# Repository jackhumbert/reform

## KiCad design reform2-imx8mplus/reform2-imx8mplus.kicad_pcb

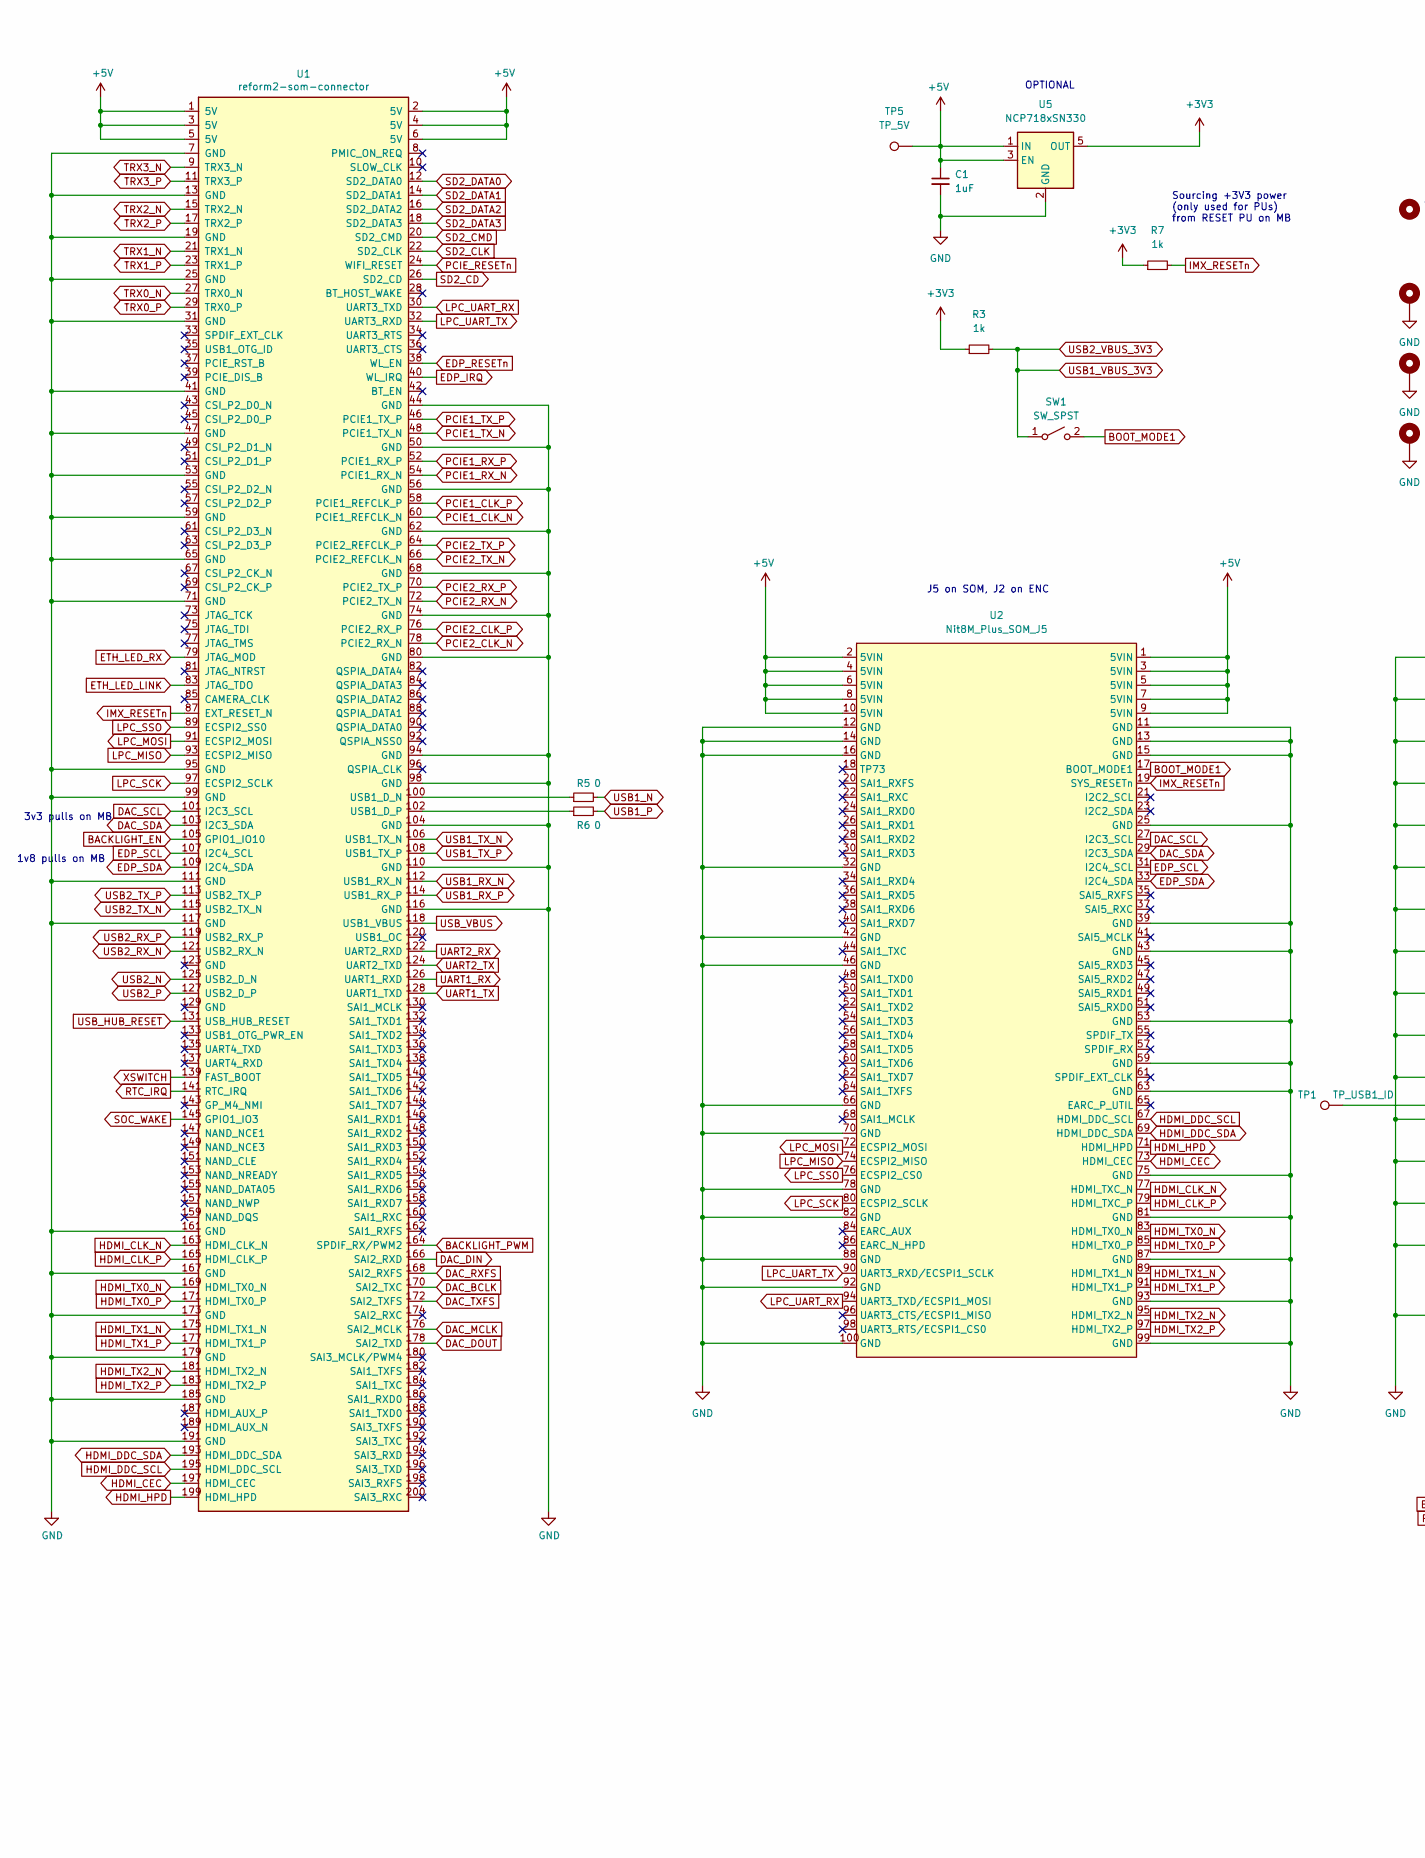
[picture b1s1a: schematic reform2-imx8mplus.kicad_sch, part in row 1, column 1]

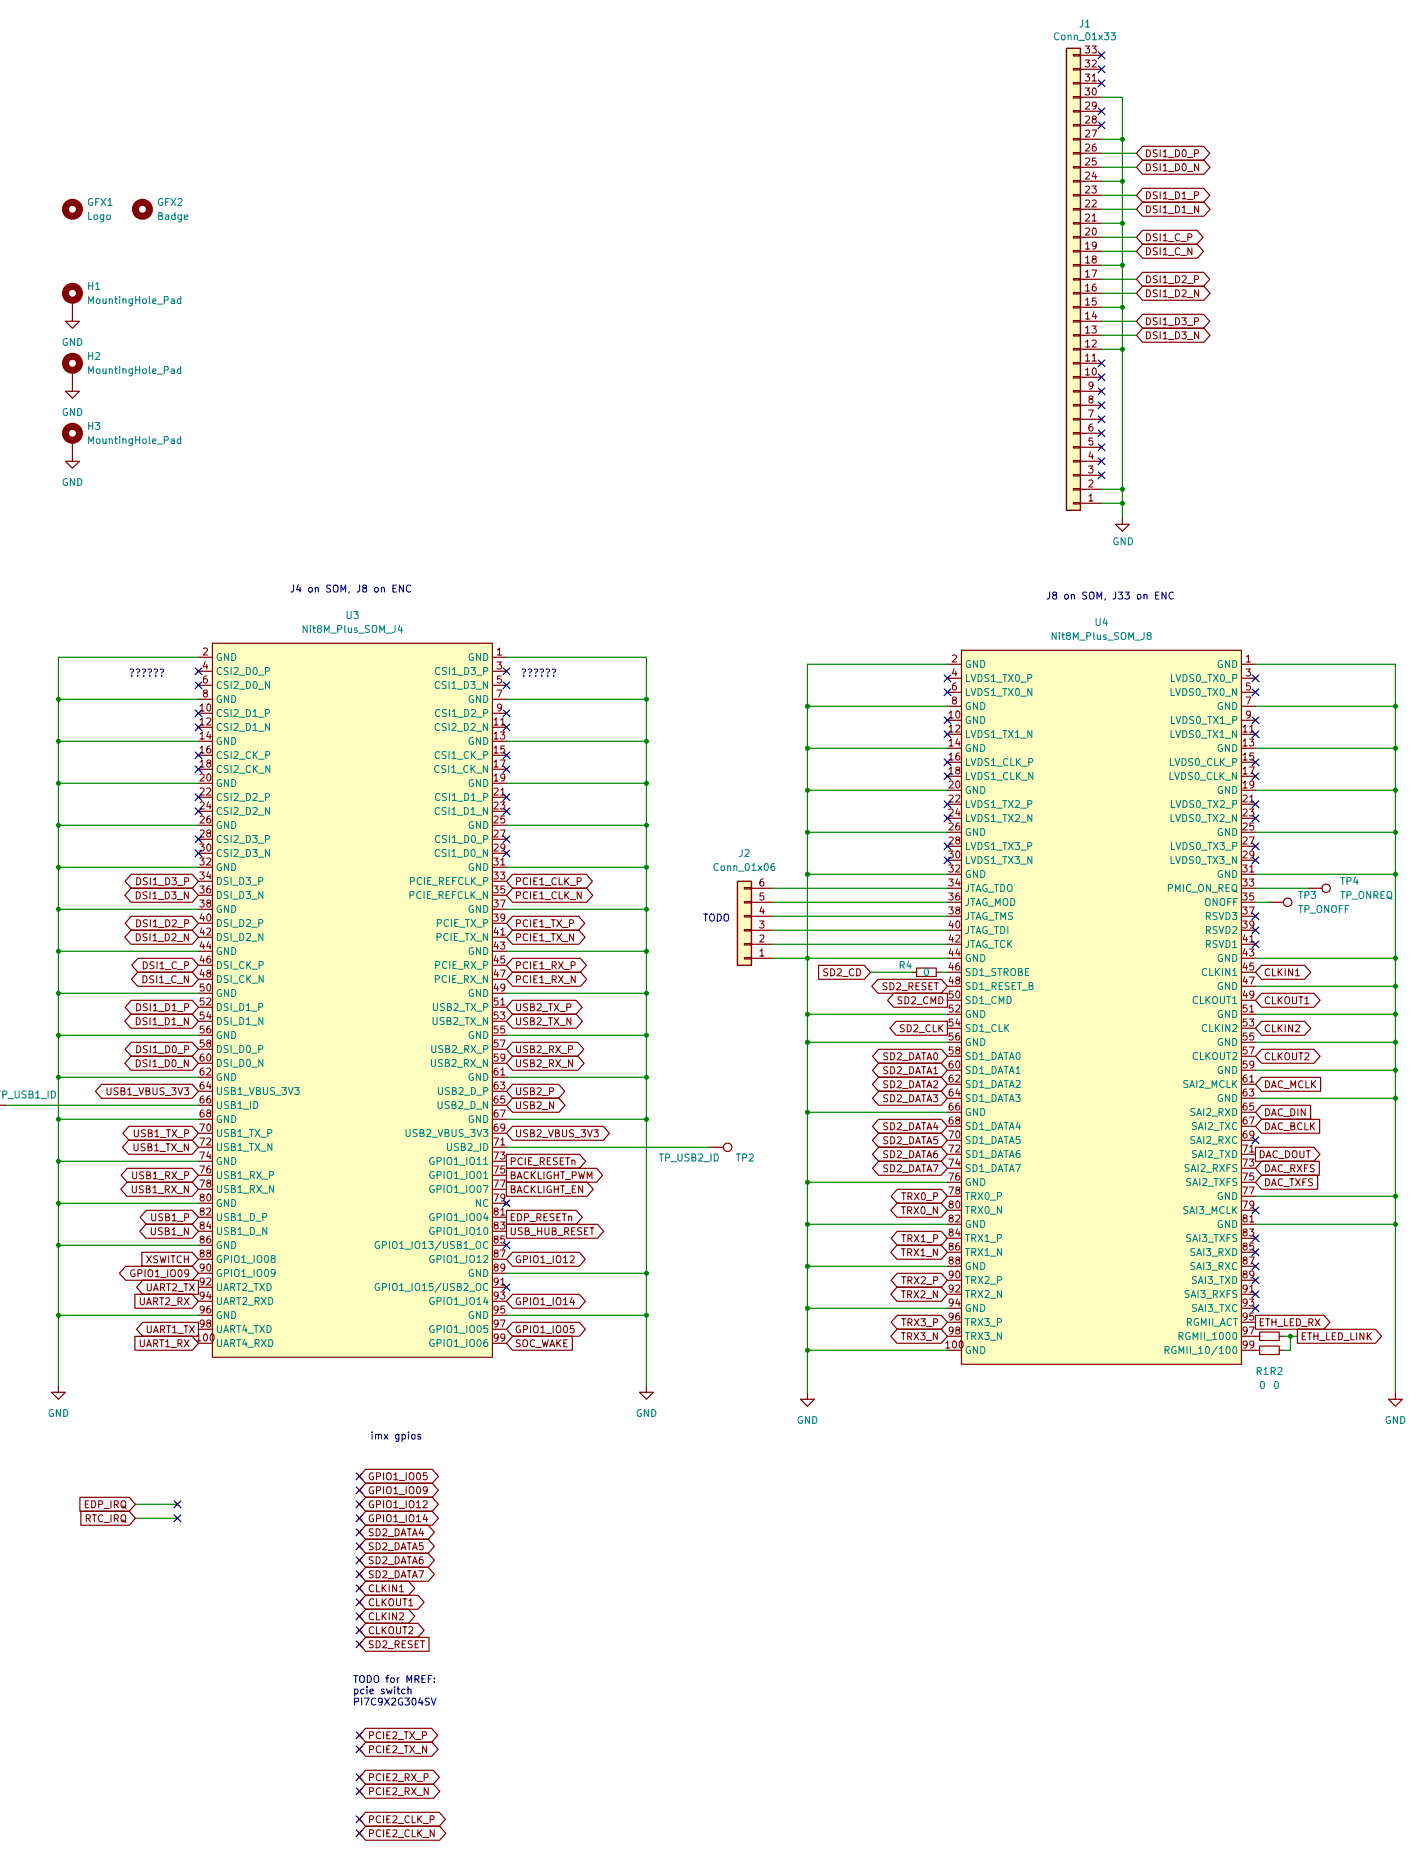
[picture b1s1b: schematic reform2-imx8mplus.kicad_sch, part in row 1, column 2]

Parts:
C1: 1uF; C_0603_1608Metric
GFX1: Logo; mntreform
GFX2: Badge; reform2-imx8mplus-badge
H1, H2, H3: MountingHole_Pad; MountingHole_2.2mm_M2_DIN965_Pad
J1: Conn_01x33; Hirose_FH12-33S-0.5SH_1x33-1MP_P0.50mm_Horizontal; MPN FH12-33S-0.5SH
J2: Conn_01x06; PinHeader_1x06_P2.00mm_Vertical
R1, R2, R5, R6: 0; R_0603_1608Metric
R3, R7: 1k; C_0603_1608Metric
R4: 0; C_0603_1608Metric
SW1: SW_SPST; PinHeader_1x02_P2.00mm_Horizontal
TP1: TP_USB1_ID; TestPoint_Pad_1.0x1.0mm
TP2: TP_USB2_ID; TestPoint_Pad_1.0x1.0mm
TP3: TP_ONOFF; TestPoint_Pad_1.0x1.0mm
TP4: TP_ONREQ; TestPoint_Pad_1.0x1.0mm
TP5: TP_5V; TestPoint_Pad_1.0x1.0mm
U1: reform2-som-connector; ddr2-sodimm200; MPN DNP
U2: Nit8M_Plus_SOM_J5; HRS_DF40C-100DS-0.4V(51)
U3: Nit8M_Plus_SOM_J4; HRS_DF40C-100DS-0.4V(51)
U4: Nit8M_Plus_SOM_J8; HRS_DF40C-100DS-0.4V(51)
U5: NCP718xSN330; SOT-23-5

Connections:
+3V3: R3.1, R7.1, U5.5 (OUT)
+5V: C1.1, TP5.1, U1.1 (5V), U1.2 (5V), U1.3 (5V), U1.4 (5V), U1.5 (5V), U1.6 (5V), U2.1 (5VIN), U2.2 (5VIN), U2.3 (5VIN), U2.4 (5VIN), U2.5 (5VIN), U2.6 (5VIN), U2.7 (5VIN), U2.8 (5VIN), U2.9 (5VIN), U2.10 (5VIN), U5.1 (IN), U5.3 (EN)
BACKLIGHT_EN: U1.105 (GPIO1_IO10), U3.77 (GPIO1_IO07)
BACKLIGHT_PWM: U1.164 (SPDIF_RX/PWM2), U3.75 (GPIO1_IO01)
BOOT_MODE1: SW1.2 (B), U2.17 (BOOT_MODE1)
CLKIN1: U4.45 (CLKIN1)
CLKIN2: U4.53 (CLKIN2)
CLKOUT1: U4.49 (CLKOUT1)
CLKOUT2: U4.57 (CLKOUT2)
DAC_BCLK: U1.170 (SAI2_TXC), U4.67 (SAI2_TXC)
DAC_DIN: U1.166 (SAI2_RXD), U4.65 (SAI2_RXD)
DAC_DOUT: U1.178 (SAI2_TXD), U4.71 (SAI2_TXD)
DAC_MCLK: U1.176 (SAI2_MCLK), U4.61 (SAI2_MCLK)
DAC_RXFS: U1.168 (SAI2_RXFS), U4.73 (SAI2_RXFS)
DAC_SCL: U1.101 (I2C3_SCL), U2.27 (I2C3_SCL)
DAC_SDA: U1.103 (I2C3_SDA), U2.29 (I2C3_SDA)
DAC_TXFS: U1.172 (SAI2_TXFS), U4.75 (SAI2_TXFS)
DSI1_C_N: J1.19, U3.48 (DSI_CK_N)
DSI1_C_P: J1.20, U3.46 (DSI_CK_P)
DSI1_D0_N: J1.25, U3.60 (DSI_D0_N)
DSI1_D0_P: J1.26, U3.58 (DSI_D0_P)
DSI1_D1_N: J1.22, U3.54 (DSI_D1_N)
DSI1_D1_P: J1.23, U3.52 (DSI_D1_P)
DSI1_D2_N: J1.16, U3.42 (DSI_D2_N)
DSI1_D2_P: J1.17, U3.40 (DSI_D2_P)
DSI1_D3_N: J1.13, U3.36 (DSI_D3_N)
DSI1_D3_P: J1.14, U3.34 (DSI_D3_P)
EDP_IRQ: U1.40 (WL_IRQ)
EDP_RESETn: U1.38 (WL_EN), U3.81 (GPIO1_IO04)
EDP_SCL: U1.107 (I2C4_SCL), U2.31 (I2C4_SCL)
EDP_SDA: U1.109 (I2C4_SDA), U2.33 (I2C4_SDA)
ETH_LED_LINK: R1.2, R2.2, U1.83 (JTAG_TDO)
ETH_LED_RX: U1.79 (JTAG_MOD), U4.95 (RGMII_ACT)
GND: C1.2, H1.1, H2.1, H3.1, J1.1, J1.2, J1.12, J1.15, J1.18, J1.21, J1.24, J1.27, J1.30, J2.1, U1.7 (GND), U1.13 (GND), U1.19 (GND), U1.25 (GND), U1.31 (GND), U1.41 (GND), U1.44 (GND), U1.47 (GND), U1.50 (GND), U1.53 (GND), U1.56 (GND), U1.59 (GND), U1.62 (GND), U1.65 (GND), U1.68 (GND), U1.71 (GND), U1.74 (GND), U1.80 (GND), U1.94 (GND), U1.95 (GND), U1.98 (GND), U1.99 (GND), U1.104 (GND), U1.110 (GND), U1.111 (GND), U1.116 (GND), U1.117 (GND), U1.161 (GND), U1.167 (GND), U1.173 (GND), U1.179 (GND), U1.185 (GND), U1.191 (GND), U2.11 (GND), U2.12 (GND), U2.13 (GND), U2.14 (GND), U2.15 (GND), U2.16 (GND), U2.25 (GND), U2.32 (GND), U2.39 (GND), U2.42 (GND), U2.43 (GND), U2.46 (GND), U2.53 (GND), U2.59 (GND), U2.63 (GND), U2.66 (GND), U2.70 (GND), U2.75 (GND), U2.78 (GND), U2.81 (GND), U2.82 (GND), U2.87 (GND), U2.88 (GND), U2.92 (GND), U2.93 (GND), U2.99 (GND), U2.100 (GND), U3.1 (GND), U3.2 (GND), U3.7 (GND), U3.8 (GND), U3.13 (GND), U3.14 (GND), U3.19 (GND), U3.20 (GND), U3.25 (GND), U3.26 (GND), U3.31 (GND), U3.32 (GND), U3.37 (GND), U3.38 (GND), U3.43 (GND), U3.44 (GND), U3.49 (GND), U3.50 (GND), U3.55 (GND), U3.56 (GND), U3.61 (GND), U3.62 (GND), U3.67 (GND), U3.68 (GND), U3.74 (GND), U3.80 (GND), U3.86 (GND), U3.89 (GND), U3.95 (GND), U3.96 (GND), U4.1 (GND), U4.2 (GND), U4.7 (GND), U4.8 (GND), U4.13 (GND), U4.14 (GND), U4.19 (GND), U4.20 (GND), U4.25 (GND), U4.26 (GND), U4.31 (GND), U4.32 (GND), U4.43 (GND), U4.44 (GND), U4.47 (GND), U4.51 (GND), U4.52 (GND), U4.55 (GND), U4.56 (GND), U4.59 (GND), U4.63 (GND), U4.66 (GND), U4.76 (GND), U4.77 (GND), U4.81 (GND), U4.82 (GND), U4.88 (GND), U4.94 (GND), U4.100 (GND), U5.2 (GND)
GPIO1_IO05: U3.97 (GPIO1_IO05)
GPIO1_IO09: U3.90 (GPIO1_IO09)
GPIO1_IO12: U3.87 (GPIO1_IO12)
GPIO1_IO14: U3.93 (GPIO1_IO14)
HDMI_CEC: U1.197 (HDMI_CEC), U2.73 (HDMI_CEC)
HDMI_CLK_N: U1.163 (HDMI_CLK_N), U2.77 (HDMI_TXC_N)
HDMI_CLK_P: U1.165 (HDMI_CLK_P), U2.79 (HDMI_TXC_P)
HDMI_DDC_SCL: U1.195 (HDMI_DDC_SCL), U2.67 (HDMI_DDC_SCL)
HDMI_DDC_SDA: U1.193 (HDMI_DDC_SDA), U2.69 (HDMI_DDC_SDA)
HDMI_HPD: U1.199 (HDMI_HPD), U2.71 (HDMI_HPD)
HDMI_TX0_N: U1.169 (HDMI_TX0_N), U2.83 (HDMI_TX0_N)
HDMI_TX0_P: U1.171 (HDMI_TX0_P), U2.85 (HDMI_TX0_P)
HDMI_TX1_N: U1.175 (HDMI_TX1_N), U2.89 (HDMI_TX1_N)
HDMI_TX1_P: U1.177 (HDMI_TX1_P), U2.91 (HDMI_TX1_P)
HDMI_TX2_N: U1.181 (HDMI_TX2_N), U2.95 (HDMI_TX2_N)
HDMI_TX2_P: U1.183 (HDMI_TX2_P), U2.97 (HDMI_TX2_P)
IMX_RESETn: R7.2, U1.87 (EXT_RESET_N), U2.19 (SYS_RESETn)
LPC_MISO: U1.93 (ECSPI2_MISO), U2.74 (ECSPI2_MISO)
LPC_MOSI: U1.91 (ECSPI2_MOSI), U2.72 (ECSPI2_MOSI)
LPC_SCK: U1.97 (ECSPI2_SCLK), U2.80 (ECSPI2_SCLK)
LPC_SSO: U1.89 (ECSPI2_SS0), U2.76 (ECSPI2_CS0)
LPC_UART_RX: U1.30 (UART3_TXD), U2.94 (UART3_TXD/ECSPI1_MOSI)
LPC_UART_TX: U1.32 (UART3_RXD), U2.90 (UART3_RXD/ECSPI1_SCLK)
unnamed: J2.2, U4.42 (JTAG_TCK)
unnamed: J2.3, U4.40 (JTAG_TDI)
unnamed: J2.4, U4.38 (JTAG_TMS)
unnamed: J2.5, U4.36 (JTAG_MOD)
unnamed: J2.6, U4.34 (JTAG_TDO)
unnamed: R1.1, U4.97 (RGMII_1000)
unnamed: R2.1, U4.99 (RGMII_10/100)
unnamed: R4.2, U4.46 (SD1_STROBE)
unnamed: R5.1, U1.100 (USB1_D_N)
unnamed: R6.1, U1.102 (USB1_D_P)
unnamed: TP1.1, U3.66 (USB1_ID)
unnamed: TP2.1, U3.71 (USB2_ID)
unnamed: TP3.1, U4.35 (ONOFF)
unnamed: TP4.1, U4.33 (PMIC_ON_REQ)
PCIE1_CLK_N: U1.60 (PCIE1_REFCLK_N), U3.35 (PCIE_REFCLK_N)
PCIE1_CLK_P: U1.58 (PCIE1_REFCLK_P), U3.33 (PCIE_REFCLK_P)
PCIE1_RX_N: U1.54 (PCIE1_RX_N), U3.47 (PCIE_RX_N)
PCIE1_RX_P: U1.52 (PCIE1_RX_P), U3.45 (PCIE_RX_P)
PCIE1_TX_N: U1.48 (PCIE1_TX_N), U3.41 (PCIE_TX_N)
PCIE1_TX_P: U1.46 (PCIE1_TX_P), U3.39 (PCIE_TX_P)
PCIE2_CLK_N: U1.78 (PCIE2_RX_N)
PCIE2_CLK_P: U1.76 (PCIE2_RX_P)
PCIE2_RX_N: U1.72 (PCIE2_TX_N)
PCIE2_RX_P: U1.70 (PCIE2_TX_P)
PCIE2_TX_N: U1.66 (PCIE2_REFCLK_N)
PCIE2_TX_P: U1.64 (PCIE2_REFCLK_P)
PCIE_RESETn: U1.24 (WIFI_RESET), U3.73 (GPIO1_IO11)
RTC_IRQ: U1.141 (RTC_IRQ)
SD2_CD: R4.1, U1.26 (SD2_CD)
SD2_CLK: U1.22 (SD2_CLK), U4.54 (SD1_CLK)
SD2_CMD: U1.20 (SD2_CMD), U4.50 (SD1_CMD)
SD2_DATA0: U1.12 (SD2_DATA0), U4.58 (SD1_DATA0)
SD2_DATA1: U1.14 (SD2_DATA1), U4.60 (SD1_DATA1)
SD2_DATA2: U1.16 (SD2_DATA2), U4.62 (SD1_DATA2)
SD2_DATA3: U1.18 (SD2_DATA3), U4.64 (SD1_DATA3)
SD2_DATA4: U4.68 (SD1_DATA4)
SD2_DATA5: U4.70 (SD1_DATA5)
SD2_DATA6: U4.72 (SD1_DATA6)
SD2_DATA7: U4.74 (SD1_DATA7)
SD2_RESET: U4.48 (SD1_RESET_B)
SOC_WAKE: U1.145 (GPIO1_IO3), U3.99 (GPIO1_IO06)
TRX0_N: U1.27 (TRX0_N), U4.80 (TRX0_N)
TRX0_P: U1.29 (TRX0_P), U4.78 (TRX0_P)
TRX1_N: U1.21 (TRX1_N), U4.86 (TRX1_N)
TRX1_P: U1.23 (TRX1_P), U4.84 (TRX1_P)
TRX2_N: U1.15 (TRX2_N), U4.92 (TRX2_N)
TRX2_P: U1.17 (TRX2_P), U4.90 (TRX2_P)
TRX3_N: U1.9 (TRX3_N), U4.98 (TRX3_N)
TRX3_P: U1.11 (TRX3_P), U4.96 (TRX3_P)
UART1_RX: U1.126 (UART1_RXD), U3.100 (UART4_RXD)
UART1_TX: U1.128 (UART1_TXD), U3.98 (UART4_TXD)
UART2_RX: U1.122 (UART2_RXD), U3.94 (UART2_RXD)
UART2_TX: U1.124 (UART2_TXD), U3.92 (UART2_TXD)
USB1_N: R5.2, U3.84 (USB1_D_N)
USB1_P: R6.2, U3.82 (USB1_D_P)
USB1_RX_N: U1.112 (USB1_RX_N), U3.78 (USB1_RX_N)
USB1_RX_P: U1.114 (USB1_RX_P), U3.76 (USB1_RX_P)
USB1_TX_N: U1.106 (USB1_TX_N), U3.72 (USB1_TX_N)
USB1_TX_P: U1.108 (USB1_TX_P), U3.70 (USB1_TX_P)
USB1_VBUS_3V3: R3.2, SW1.1 (A), U3.64 (USB1_VBUS_3V3), U3.69 (USB2_VBUS_3V3)
USB2_N: U1.125 (USB2_D_N), U3.65 (USB2_D_N)
USB2_P: U1.127 (USB2_D_P), U3.63 (USB2_D_P)
USB2_RX_N: U1.121 (USB2_RX_N), U3.59 (USB2_RX_N)
USB2_RX_P: U1.119 (USB2_RX_P), U3.57 (USB2_RX_P)
USB2_TX_N: U1.115 (USB2_TX_N), U3.53 (USB2_TX_N)
USB2_TX_P: U1.113 (USB2_TX_P), U3.51 (USB2_TX_P)
USB_HUB_RESET: U1.131 (USB_HUB_RESET), U3.83 (GPIO1_IO10)
USB_VBUS: U1.118 (USB1_VBUS)
XSWITCH: U1.139 (FAST_BOOT), U3.88 (GPIO1_IO08)

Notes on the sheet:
J4 on SOM, J8 on ENC
3v3 pulls on MB
OPTIONAL
imx gpios
1v8 pulls on MB
J8 on SOM, J33 on ENC
??????
TODO
J5 on SOM, J2 on ENC
Sourcing +3V3 power (only used for PUs) from RESET PU on MB
TODO for MREF: pcie switch PI7C9X2G304SV

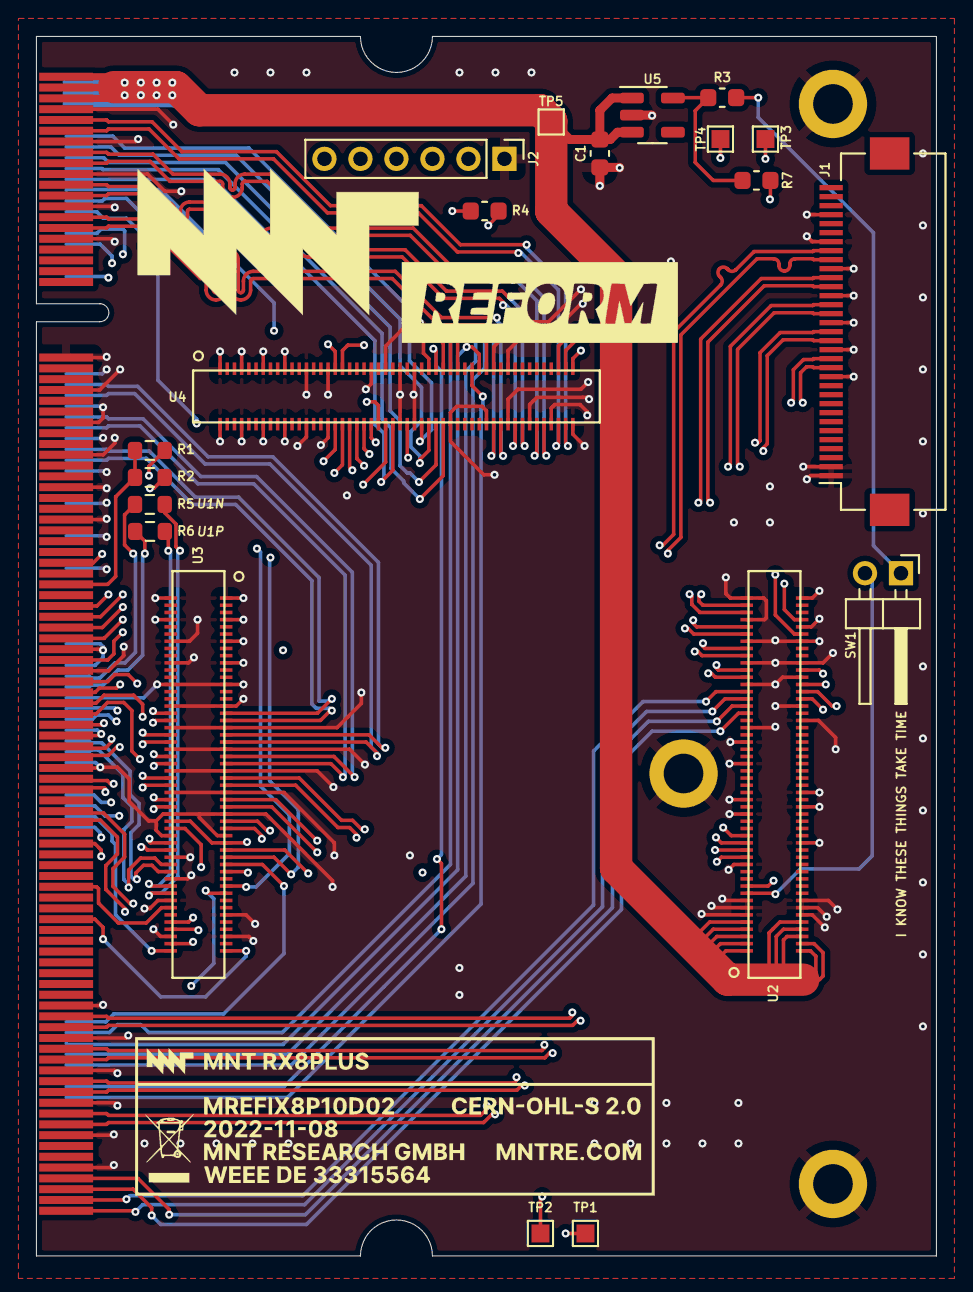
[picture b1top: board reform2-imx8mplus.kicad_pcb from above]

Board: 6 copper layers, 50.0 x 67.8 mm, 26 parts (0 on the bottom side), 104 nets.

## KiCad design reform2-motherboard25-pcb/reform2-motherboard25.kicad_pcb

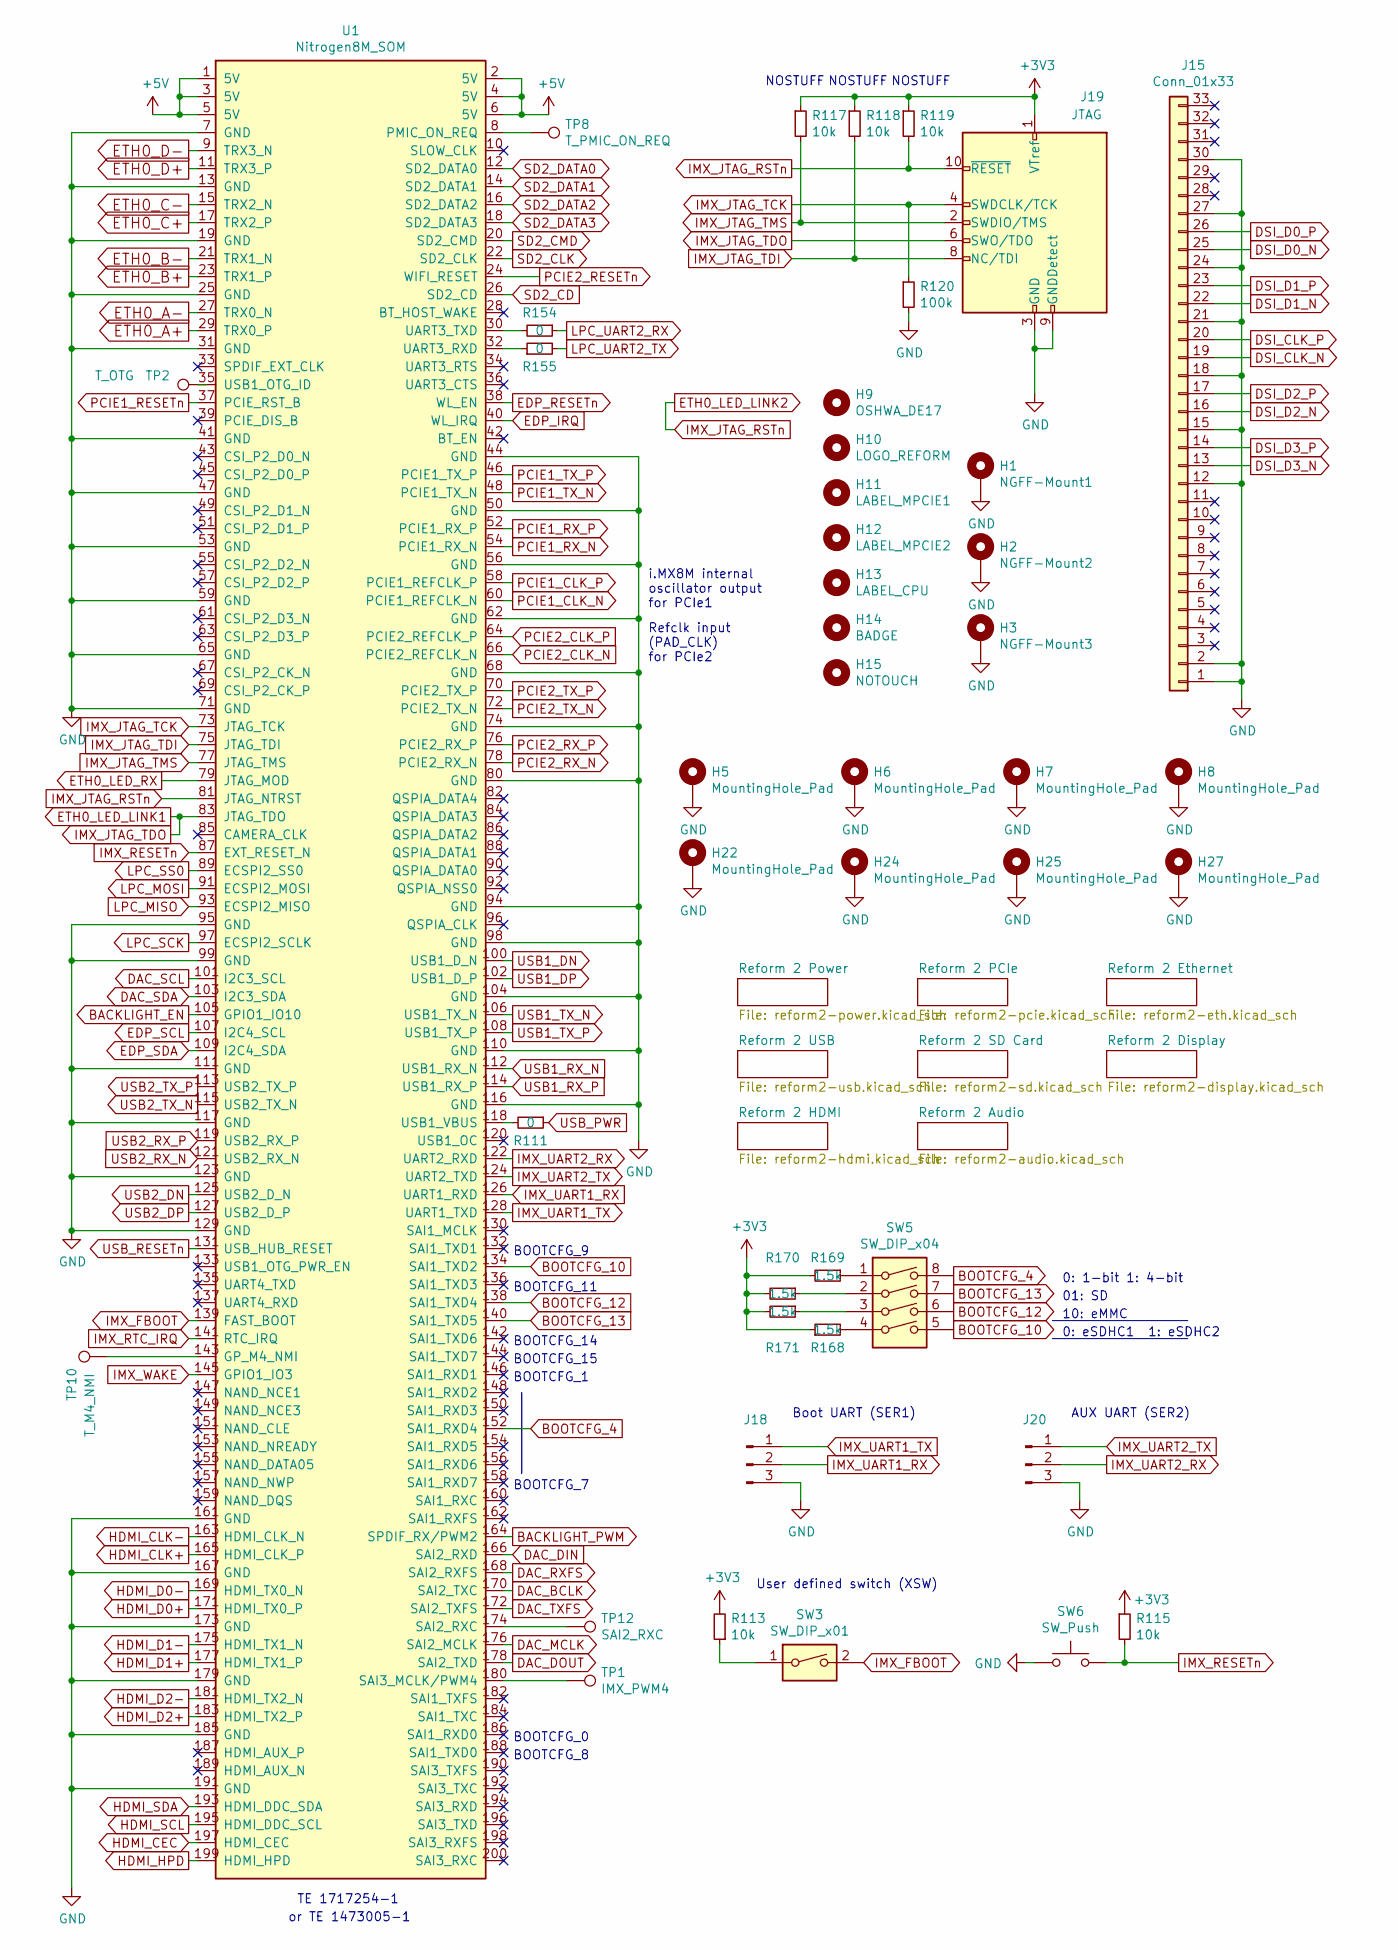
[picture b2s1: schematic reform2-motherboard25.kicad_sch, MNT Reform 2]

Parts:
H1: NGFF-Mount1; WA-SMSI-M2
H2: NGFF-Mount2; WA-SMSI-M2
H3: NGFF-Mount3; WA-SMSI-M2
H5, H6, H7, H8: MountingHole_Pad; MountingHole_2.2mm_M2_DIN965_Pad
H9: OSHWA_DE17; oshwa-de17
H10: LOGO_REFORM; mntreform
H11: LABEL_MPCIE1; mpcie
H12: LABEL_MPCIE2; nvme
H13: LABEL_CPU; cpu
H14: BADGE; reform2-motherboard-badge
H15: NOTOUCH; ESD-Logo_8.9x8mm_SilkScreen
H22, H24, H25, H27: MountingHole_Pad; WA-SMSI-M2
J15: Conn_01x33; Hirose_FH12-33S-0.5SH_1x33-1MP_P0.50mm_Horizontal
J18: Conn_01x03_Male; PinHeader_1x03_P2.54mm_Horizontal
J19: JTAG; PinHeader_2x05_P1.27mm_Vertical
J20: Conn_01x03_Male; PinHeader_1x03_P2.54mm_Vertical
R111, R154, R155: 0; R_0603_1608Metric
R113, R115, R117, R118, R119: 10k; R_0603_1608Metric
R120: 100k; R_0603_1608Metric
R168, R169, R170, R171: 1.5k; R_0603_1608Metric
SW3: SW_DIP_x01; SW_DIP_SPSTx01_Slide_Omron_A6S-110x_W8.9mm_P2.54mm
SW5: SW_DIP_x04; SW_DIP_SPSTx04_Slide_Copal_CHS-04B_W7.62mm_P1.27mm
SW6: SW_Push; UK-B0206-G3.8-250-JZ
TP1: IMX_PWM4; TestPoint_Pad_D1.0mm
TP2: T_OTG; TestPoint_Pad_D1.0mm
TP8: T_PMIC_ON_REQ; TestPoint_Pad_D1.0mm
TP10: T_M4_NMI; TestPoint_Pad_D1.0mm
TP12: SAI2_RXC; TestPoint_Pad_D1.0mm
U1: Nitrogen8M_SOM; TE_1473149-4

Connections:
+3V3: J19.1 (VTref), R113.2, R115.1, R117.1, R118.1, R119.1, R168.1, R169.2, R170.2, R171.2; also elsewhere on the board
+5V: U1.1 (5V), U1.2 (5V), U1.3 (5V), U1.4 (5V), U1.5 (5V), U1.6 (5V); also elsewhere on the board
BACKLIGHT_EN: U1.105 (GPIO1_IO10); also elsewhere on the board
BACKLIGHT_PWM: U1.164 (SPDIF_RX/PWM2); also elsewhere on the board
BOOTCFG_4: SW5.8, U1.152 (SAI1_RXD4)
BOOTCFG_10: SW5.5, U1.134 (SAI1_TXD2)
BOOTCFG_12: SW5.6, U1.138 (SAI1_TXD4)
BOOTCFG_13: SW5.7, U1.140 (SAI1_TXD5)
DAC_BCLK: U1.170 (SAI2_TXC); also elsewhere on the board
DAC_DIN: U1.166 (SAI2_RXD); also elsewhere on the board
DAC_DOUT: U1.178 (SAI2_TXD); also elsewhere on the board
DAC_MCLK: U1.176 (SAI2_MCLK); also elsewhere on the board
DAC_RXFS: U1.168 (SAI2_RXFS); also elsewhere on the board
DAC_SCL: U1.101 (I2C3_SCL); also elsewhere on the board
DAC_SDA: U1.103 (I2C3_SDA); also elsewhere on the board
DAC_TXFS: U1.172 (SAI2_TXFS); also elsewhere on the board
DSI_CLK_N: J15.19; also elsewhere on the board
DSI_CLK_P: J15.20; also elsewhere on the board
DSI_D0_N: J15.25; also elsewhere on the board
DSI_D0_P: J15.26; also elsewhere on the board
DSI_D1_N: J15.22; also elsewhere on the board
DSI_D1_P: J15.23; also elsewhere on the board
DSI_D2_N: J15.16; also elsewhere on the board
DSI_D2_P: J15.17; also elsewhere on the board
DSI_D3_N: J15.13; also elsewhere on the board
DSI_D3_P: J15.14; also elsewhere on the board
EDP_IRQ: U1.40 (WL_IRQ); also elsewhere on the board
EDP_RESETn: U1.38 (WL_EN); also elsewhere on the board
EDP_SCL: U1.107 (I2C4_SCL); also elsewhere on the board
EDP_SDA: U1.109 (I2C4_SDA); also elsewhere on the board
ETH0_A+: U1.29 (TRX0_P); also elsewhere on the board
ETH0_A-: U1.27 (TRX0_N); also elsewhere on the board
ETH0_B+: U1.23 (TRX1_P); also elsewhere on the board
ETH0_B-: U1.21 (TRX1_N); also elsewhere on the board
ETH0_C+: U1.17 (TRX2_P); also elsewhere on the board
ETH0_C-: U1.15 (TRX2_N); also elsewhere on the board
ETH0_D+: U1.11 (TRX3_P); also elsewhere on the board
ETH0_D-: U1.9 (TRX3_N); also elsewhere on the board
ETH0_LED_LINK1: J19.6 (SWO/TDO), U1.83 (JTAG_TDO); also elsewhere on the board
ETH0_LED_LINK2: J19.10 (~RESET), R119.2, U1.81 (JTAG_NTRST); also elsewhere on the board
ETH0_LED_RX: U1.79 (JTAG_MOD); also elsewhere on the board
GND: H1.1, H2.1, H3.1, H5.1, H6.1, H7.1, H8.1, H22.1, H24.1, H25.1, H27.1, J15.1, J15.2, J15.12, J15.15, J15.18, J15.21, J15.24, J15.27, J15.30, J18.3, J19.3 (GND), J19.5 (GND), J19.9 (GNDDetect), J20.3, R120.2, SW6.1, U1.7 (GND), U1.13 (GND), U1.19 (GND), U1.25 (GND), U1.31 (GND), U1.41 (GND), U1.44 (GND), U1.47 (GND), U1.50 (GND), U1.53 (GND), U1.56 (GND), U1.59 (GND), U1.62 (GND), U1.65 (GND), U1.68 (GND), U1.71 (GND), U1.74 (GND), U1.80 (GND), U1.94 (GND), U1.95 (GND), U1.98 (GND), U1.99 (GND), U1.104 (GND), U1.110 (GND), U1.111 (GND), U1.116 (GND), U1.117 (GND), U1.123 (GND), U1.129 (GND), U1.161 (GND), U1.167 (GND), U1.173 (GND), U1.179 (GND), U1.185 (GND), U1.191 (GND); also elsewhere on the board
HDMI_CEC: U1.197 (HDMI_CEC); also elsewhere on the board
HDMI_CLK+: U1.165 (HDMI_CLK_P); also elsewhere on the board
HDMI_CLK-: U1.163 (HDMI_CLK_N); also elsewhere on the board
HDMI_D0+: U1.171 (HDMI_TX0_P); also elsewhere on the board
HDMI_D0-: U1.169 (HDMI_TX0_N); also elsewhere on the board
HDMI_D1+: U1.177 (HDMI_TX1_P); also elsewhere on the board
HDMI_D1-: U1.175 (HDMI_TX1_N); also elsewhere on the board
HDMI_D2+: U1.183 (HDMI_TX2_P); also elsewhere on the board
HDMI_D2-: U1.181 (HDMI_TX2_N); also elsewhere on the board
HDMI_HPD: U1.199 (HDMI_HPD); also elsewhere on the board
HDMI_SCL: U1.195 (HDMI_DDC_SCL); also elsewhere on the board
HDMI_SDA: U1.193 (HDMI_DDC_SDA); also elsewhere on the board
IMX_FBOOT: SW3.2, U1.139 (FAST_BOOT)
IMX_JTAG_TCK: J19.4 (SWDCLK/TCK), R120.1, U1.73 (JTAG_TCK)
IMX_JTAG_TDI: J19.8 (NC/TDI), R118.2, U1.75 (JTAG_TDI)
IMX_JTAG_TMS: J19.2 (SWDIO/TMS), R117.2, U1.77 (JTAG_TMS)
IMX_RESETn: R115.2, SW6.2, U1.87 (EXT_RESET_N); also elsewhere on the board
IMX_RTC_IRQ: U1.141 (RTC_IRQ); also elsewhere on the board
IMX_UART1_RX: J18.2, U1.126 (UART1_RXD)
IMX_UART1_TX: J18.1, U1.128 (UART1_TXD)
IMX_UART2_RX: J20.2, U1.122 (UART2_RXD)
IMX_UART2_TX: J20.1, U1.124 (UART2_TXD)
IMX_WAKE: U1.145 (GPIO1_IO3); also elsewhere on the board
LPC_MISO: U1.93 (ECSPI2_MISO); also elsewhere on the board
LPC_MOSI: U1.91 (ECSPI2_MOSI); also elsewhere on the board
LPC_SCK: U1.97 (ECSPI2_SCLK); also elsewhere on the board
LPC_SS0: U1.89 (ECSPI2_SS0); also elsewhere on the board
LPC_UART2_RX: R154.1; also elsewhere on the board
LPC_UART2_TX: R155.2; also elsewhere on the board
unnamed: R111.2, U1.118 (USB1_VBUS)
unnamed: R113.1, SW3.1
unnamed: R154.2, U1.30 (UART3_TXD)
unnamed: R155.1, U1.32 (UART3_RXD)
unnamed: R168.2, SW5.4
unnamed: R169.1, SW5.1
unnamed: R170.1, SW5.2
unnamed: R171.1, SW5.3
unnamed: TP1.1, U1.180 (SAI3_MCLK/PWM4)
unnamed: TP2.1, U1.35 (USB1_OTG_ID)
unnamed: TP8.1, U1.8 (PMIC_ON_REQ)
unnamed: TP10.1, U1.143 (GP_M4_NMI)
unnamed: TP12.1, U1.174 (SAI2_RXC)
PCIE1_CLK_N: U1.60 (PCIE1_REFCLK_N); also elsewhere on the board
PCIE1_CLK_P: U1.58 (PCIE1_REFCLK_P); also elsewhere on the board
PCIE1_RESETn: U1.37 (PCIE_RST_B); also elsewhere on the board
PCIE1_RX_N: U1.54 (PCIE1_RX_N); also elsewhere on the board
PCIE1_RX_P: U1.52 (PCIE1_RX_P); also elsewhere on the board
PCIE1_TX_N: U1.48 (PCIE1_TX_N); also elsewhere on the board
PCIE1_TX_P: U1.46 (PCIE1_TX_P); also elsewhere on the board
PCIE2_CLK_N: U1.66 (PCIE2_REFCLK_N); also elsewhere on the board
PCIE2_CLK_P: U1.64 (PCIE2_REFCLK_P); also elsewhere on the board
PCIE2_RESETn: U1.24 (WIFI_RESET); also elsewhere on the board
PCIE2_RX_N: U1.78 (PCIE2_RX_N); also elsewhere on the board
PCIE2_RX_P: U1.76 (PCIE2_RX_P); also elsewhere on the board
PCIE2_TX_N: U1.72 (PCIE2_TX_N); also elsewhere on the board
PCIE2_TX_P: U1.70 (PCIE2_TX_P); also elsewhere on the board
SD2_CD: U1.26 (SD2_CD); also elsewhere on the board
SD2_CLK: U1.22 (SD2_CLK); also elsewhere on the board
SD2_CMD: U1.20 (SD2_CMD); also elsewhere on the board
SD2_DATA0: U1.12 (SD2_DATA0); also elsewhere on the board
SD2_DATA1: U1.14 (SD2_DATA1); also elsewhere on the board
SD2_DATA2: U1.16 (SD2_DATA2); also elsewhere on the board
SD2_DATA3: U1.18 (SD2_DATA3); also elsewhere on the board
USB1_DN: U1.100 (USB1_D_N); also elsewhere on the board
USB1_DP: U1.102 (USB1_D_P); also elsewhere on the board
USB1_RX_N: U1.112 (USB1_RX_N)
USB1_RX_P: U1.114 (USB1_RX_P)
USB1_TX_N: U1.106 (USB1_TX_N)
USB1_TX_P: U1.108 (USB1_TX_P)
USB2_DN: U1.125 (USB2_D_N); also elsewhere on the board
USB2_DP: U1.127 (USB2_D_P); also elsewhere on the board
USB2_RX_N: U1.121 (USB2_RX_N); also elsewhere on the board
USB2_RX_P: U1.119 (USB2_RX_P); also elsewhere on the board
USB2_TX_N: U1.115 (USB2_TX_N); also elsewhere on the board
USB2_TX_P: U1.113 (USB2_TX_P); also elsewhere on the board
USB_PWR: R111.1; also elsewhere on the board
USB_RESETn: U1.131 (USB_HUB_RESET); also elsewhere on the board

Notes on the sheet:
NOSTUFF
01: SD
BOOTCFG_7
BOOTCFG_0
10: eMMC
TE 1717254-1
BOOTCFG_9
Boot UART (SER1)
User defined switch (XSW)
BOOTCFG_14
BOOTCFG_15
0: 1-bit 1: 4-bit
BOOTCFG_1
BOOTCFG_11
BOOTCFG_8
i.MX8M internal oscillator output for PCIe1
Refclk input (PAD_CLK) for PCIe2
or TE 1473005-1
AUX UART (SER2)
0: eSDHC1 1: eSDHC2

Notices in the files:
reform2-batterypack-pcb/reform2-batterypack-upstream.sch:
License: CERN-OHL-S 2.0
reform2-keyboard-pcb/reform-kbd-mcu.sch:
Copyright 2017-2022 MNT Research GmbH
reform2-keyboard-pcb/reform2-keyboard-backlight.sch:
Copyright 2017-2020 MNT Research GmbH
